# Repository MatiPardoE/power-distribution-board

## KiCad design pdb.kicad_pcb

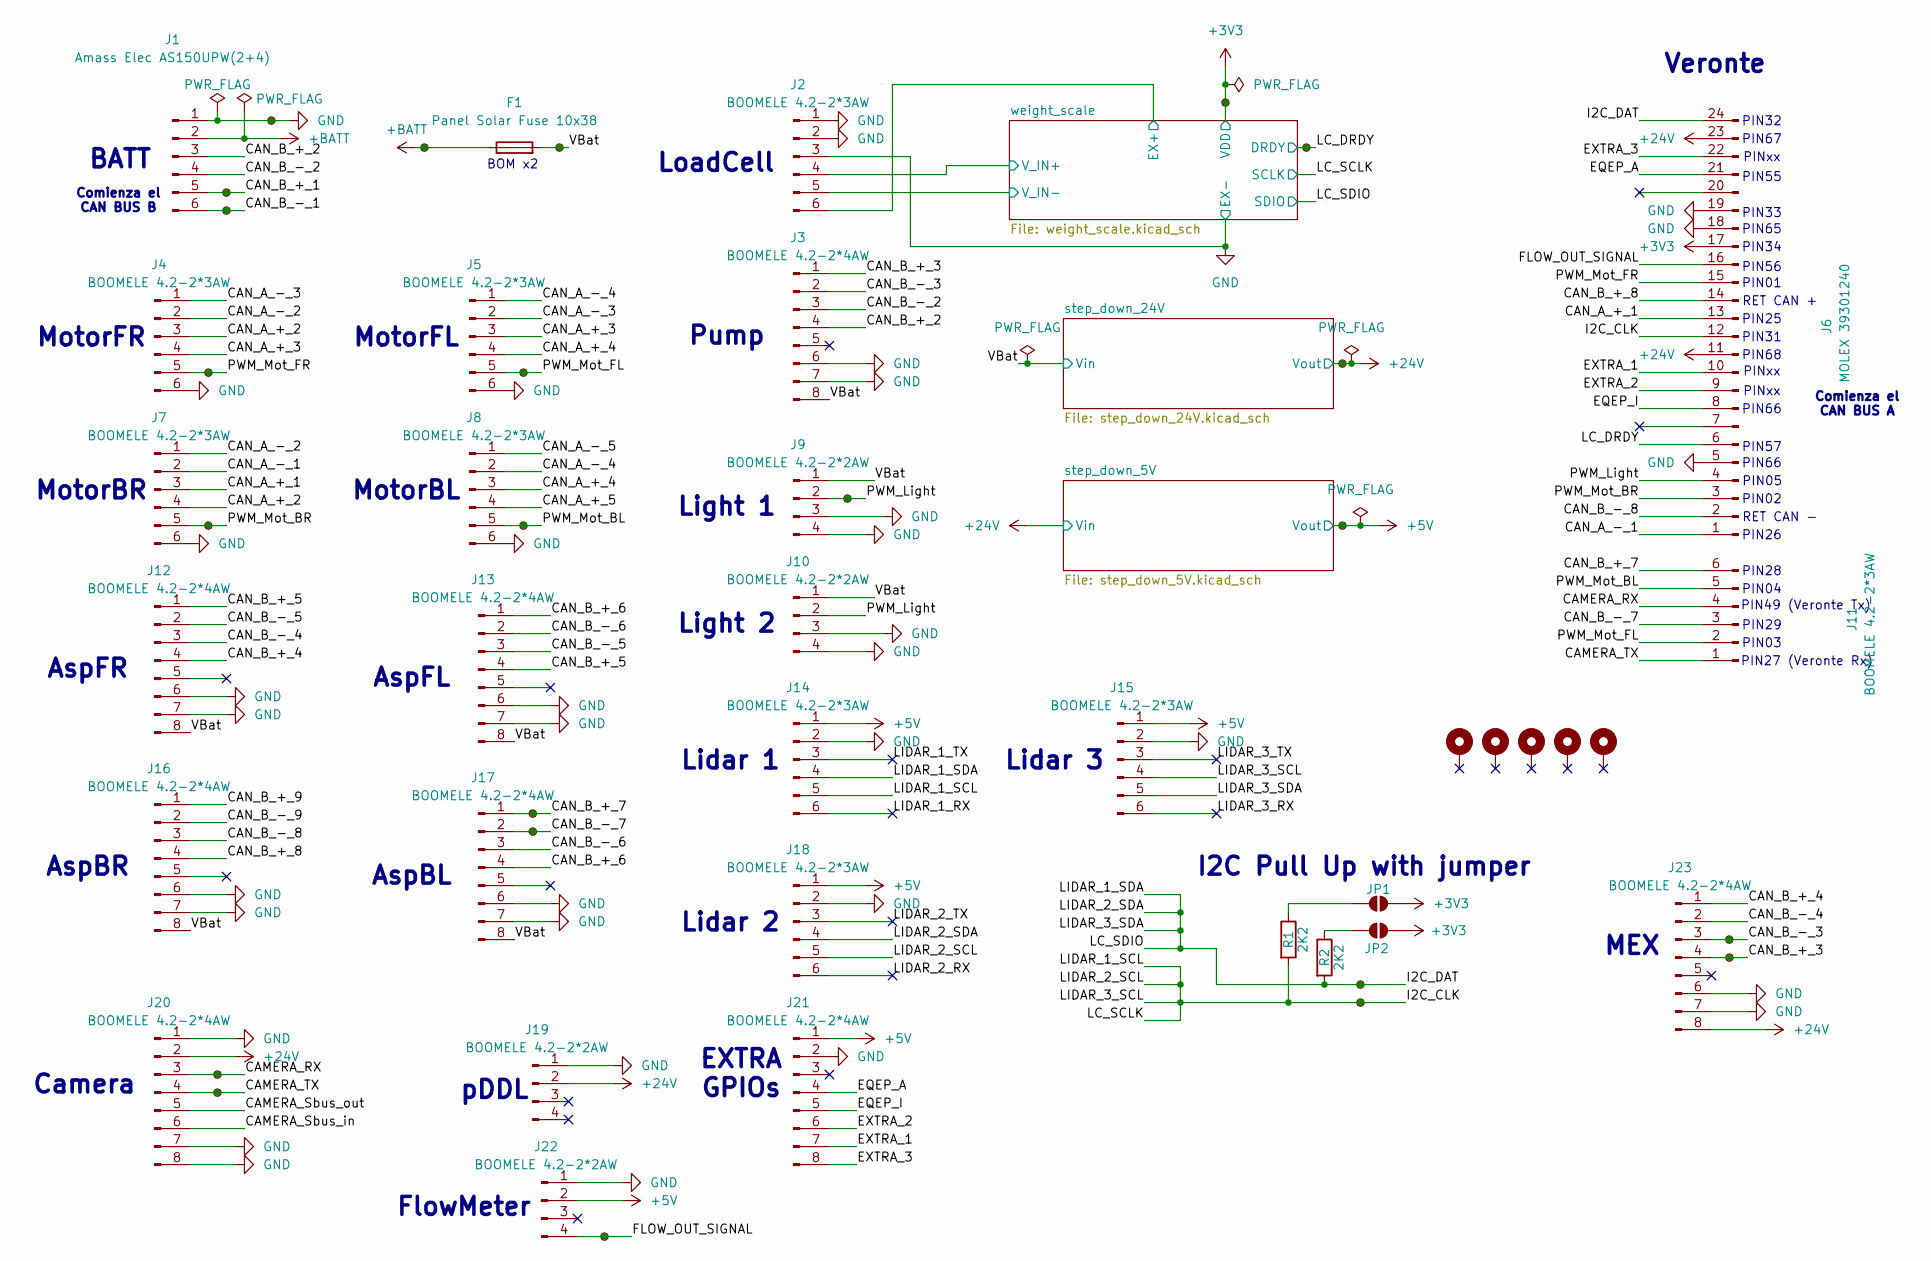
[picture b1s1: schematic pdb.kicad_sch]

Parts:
F1: Panel Solar Fuse 10x38; FUSE-HOLDER XFCN XF-008; LCSC Part # C717029
H1, H2, H3, H4, H5: MountingHole_Pad; MountingHole_3.2mm_M3_Pad_Via
J1: Amass Elec AS150UPW(2+4); CONN-TH_AS150UPW; LCSC Part # C19268054
J2, J4, J5, J7, J8, J11, J14, J15, J18: BOOMELE 4.2-2*3AW; Molex_Mini-Fit_Jr_5569-06A2_2x03_P4.20mm_Horizontal; LCSC Part # C54904
J3, J12, J13, J16, J17, J20, J21, J23: BOOMELE 4.2-2*4AW; Molex_Mini-Fit_Jr_5569-08A2_2x04_P4.20mm_Horizontal; LCSC Part # C44253
J6: MOLEX 39301240; Molex_Mini-Fit_Jr_5569-24A2_2x12_P4.20mm_Horizontal; LCSC Part # C492347
J9, J10, J19, J22: BOOMELE 4.2-2*2AW; Molex_Mini-Fit_Jr_5569-04A2_2x02_P4.20mm_Horizontal; LCSC Part # C54909
JP1, JP2: SolderJumper_2_Open; SolderJumper-2_P1.3mm_Open_TrianglePad1.0x1.5mm
R1, R2: 2K2; R_1206_3216Metric; LCSC Part # C2907443
TP1: +BATT; TestPoint_Pad_D2.0mm_silk_value
TP2: VBat; TestPoint_Pad_D2.0mm_silk_value
TP3: GND; TestPoint_Pad_D2.0mm_silk_value
TP4: CAN_B_+_1; TestPoint_Pad_D2.0mm_silk_value
TP5: CAN_B_-_1; TestPoint_Pad_D2.0mm_silk_value
TP8: CAN_B_+_7; TestPoint_Pad_D2.0mm_silk_value
TP9: CAN_B_-_7; TestPoint_Pad_D2.0mm_silk_value
TP12: CAM_RX; TestPoint_Pad_D2.0mm_silk_value
TP13: CAM_TX; TestPoint_Pad_D2.0mm_silk_value
TP14: PWM_MOT_FR; TestPoint_Pad_D2.0mm_silk_value
TP15: PWM_MOT_BR; TestPoint_Pad_D2.0mm_silk_value
TP16: PWM_MOT_BL; TestPoint_Pad_D2.0mm_silk_value
TP17: PWM_MOT_FL; TestPoint_Pad_D2.0mm_silk_value
TP18: FLOW_S; TestPoint_Pad_D2.0mm_silk_value
TP19: PWM_LIGHT; TestPoint_Pad_D2.0mm_silk_value
TP20: +24V; TestPoint_Pad_D2.0mm_silk_value
TP21: +5V; TestPoint_Pad_D2.0mm_silk_value
TP22: +3V3; TestPoint_Pad_D2.0mm_silk_value
TP23: I2C_DAT; TestPoint_Pad_D2.0mm_silk_value
TP24: I2C_CLK; TestPoint_Pad_D2.0mm_silk_value
TP27: LC_DRDY; TestPoint_Pad_D2.0mm_silk_value
TP28: CAN_B_-_3; TestPoint_Pad_D2.0mm_silk_value
TP29: CAN_B_+_3; TestPoint_Pad_D2.0mm_silk_value

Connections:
+3V3: J6.17, JP1.2 (B), JP2.2 (B), TP22.1; also elsewhere on the board
+5V: J14.1, J15.1, J18.1, J21.1, J22.2, TP21.1; also elsewhere on the board
+24V: J6.11, J6.23, J19.2, J20.2, J23.8, TP20.1; also elsewhere on the board
+BATT: F1.1, J1.2, TP1.1
/CAMERA_RX: J11.4, J20.3, TP12.1
/CAMERA_Sbus_in: J20.6
/CAMERA_Sbus_out: J20.5
/CAMERA_TX: J11.1, J20.4, TP13.1
/CAN_A_+_1: J6.13, J7.3
/CAN_A_+_2: J4.3, J7.4
/CAN_A_+_3: J4.4, J5.3
/CAN_A_+_4: J5.4, J8.3
/CAN_A_+_5: J8.4
/CAN_A_-_1: J6.1, J7.2
/CAN_A_-_2: J4.2, J7.1
/CAN_A_-_3: J4.1, J5.2
/CAN_A_-_4: J5.1, J8.2
/CAN_A_-_5: J8.1
/CAN_B_+_1: J1.5, TP4.1
/CAN_B_+_2: J1.3, J3.4
/CAN_B_+_3: J3.1, J23.4, TP29.1
/CAN_B_+_4: J12.4, J23.1
/CAN_B_+_5: J12.1, J13.4
/CAN_B_+_6: J13.1, J17.4
/CAN_B_+_7: J11.6, J17.1, TP8.1
/CAN_B_+_8: J6.14, J16.4
/CAN_B_+_9: J16.1
/CAN_B_-_1: J1.6, TP5.1
/CAN_B_-_2: J1.4, J3.3
/CAN_B_-_3: J3.2, J23.3, TP28.1
/CAN_B_-_4: J12.3, J23.2
/CAN_B_-_5: J12.2, J13.3
/CAN_B_-_6: J13.2, J17.3
/CAN_B_-_7: J11.3, J17.2, TP9.1
/CAN_B_-_8: J6.2, J16.3
/CAN_B_-_9: J16.2
/EQEP_A: J6.21, J21.4
/EQEP_I: J6.8, J21.5
/EXTRA_1: J6.10, J21.7
/EXTRA_2: J6.9, J21.6
/EXTRA_3: J6.22, J21.8
/FLOW_OUT_SIGNAL: J6.16, J22.4, TP18.1
/I2C_CLK: J6.12, J14.5, J15.4, J18.5, R1.2, TP24.1; also elsewhere on the board
/I2C_DAT: J6.24, J14.4, J15.5, J18.4, R2.2, TP23.1; also elsewhere on the board
/LC_DRDY: J6.6, TP27.1; also elsewhere on the board
/LIDAR_1_RX: J14.6
/LIDAR_1_TX: J14.3
/LIDAR_2_RX: J18.6
/LIDAR_2_TX: J18.3
/LIDAR_3_RX: J15.6
/LIDAR_3_TX: J15.3
/PWM_Light: J6.4, J9.2, J10.2, TP19.1
/PWM_Mot_BL: J8.5, J11.5, TP16.1
/PWM_Mot_BR: J6.3, J7.5, TP15.1
/PWM_Mot_FL: J5.5, J11.2, TP17.1
/PWM_Mot_FR: J4.5, J6.15, TP14.1
/VBat: F1.2, J3.8, J9.1, J10.1, J12.8, J13.8, J16.8, J17.8, TP2.1; also elsewhere on the board
/weight_scale/EX+: J2.6; also elsewhere on the board
/weight_scale/V_IN+: J2.4; also elsewhere on the board
/weight_scale/V_IN-: J2.5; also elsewhere on the board
GND: J1.1, J2.1, J2.2, J2.3, J3.6, J3.7, J4.6, J5.6, J6.5, J6.18, J6.19, J7.6, J8.6, J9.3, J9.4, J10.3, J10.4, J12.6, J12.7, J13.6, J13.7, J14.2, J15.2, J16.6, J16.7, J17.6, J17.7, J18.2, J19.1, J20.1, J20.7, J20.8, J21.2, J22.1, J23.6, J23.7, TP3.1; also elsewhere on the board
unnamed: JP1.1 (A), R1.1
unnamed: JP2.1 (A), R2.1

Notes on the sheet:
AspBR
FlowMeter
PIN66
PIN49 (Veronte Tx)
AspFR
PIN02
AspFL
PIN33
PIN01
PIN67
PIN56
PIN68
PINxx
Lidar 3
Light 1
Comienza el CAN BUS A
LoadCell
Lidar 1
I2C Pull Up with jumper
pDDL
MotorBR
Lidar 2
EXTRA GPIOs
Comienza el CAN BUS B
MotorBL
PIN32
PIN04
PIN57
PIN29
PIN31
MotorFR
MEX
PIN26
PIN27 (Veronte Rx)
PIN05
PIN28
Pump
Veronte
PIN55
Camera

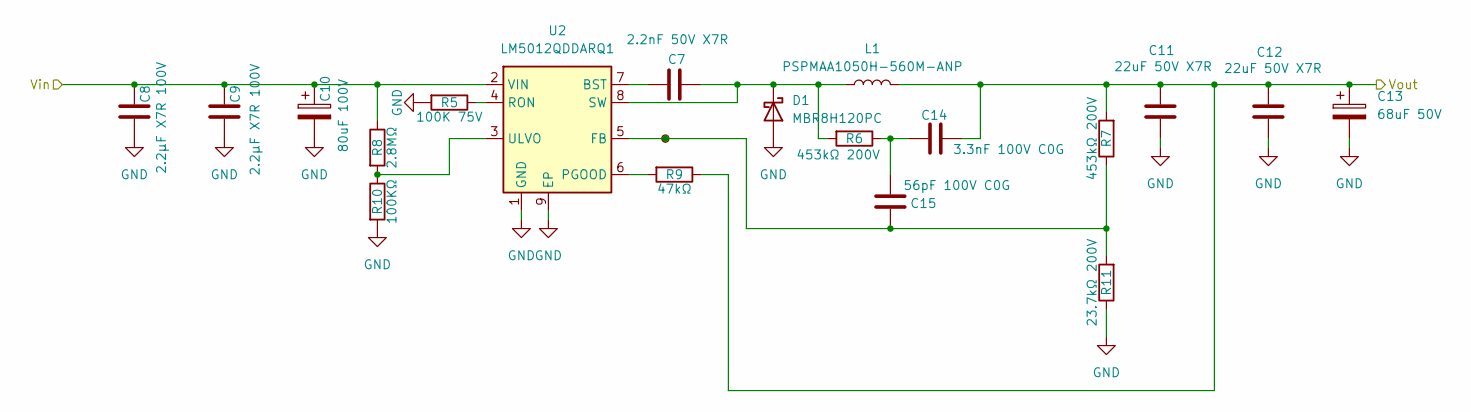
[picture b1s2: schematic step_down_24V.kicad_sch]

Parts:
C7: 2.2nF 50V X7R; C_0603_1608Metric; LCSC Part # C86023
C8, C9: 2.2µF X7R 100V; C_1206_3216Metric; LCSC Part # C577211
C10: 80uF 100V; CP_Elec_10x10.5; LCSC Part # C22387789
C11, C12: 22uF 50V X7R; C_1812_4532Metric; LCSC Part # C22388553
C13: 68uF 50V; CP_Elec_6.3x7.7; LCSC Part # C5221836
C14: 3.3nF 100V C0G; C_1206_3216Metric; LCSC Part # C2915710
C15: 56pF 100V C0G; C_0603_1608Metric; LCSC Part # C490535
D1: MBR8H120PC; TO-277C; LCSC Part # C19845038
L1: PSPMAA1050H-560M-ANP; L_Sunlord_MWSA1005S; LCSC Part # C5273831
R5: 100K 75V; R_0603_1608Metric; LCSC Part # C25803
R6, R7: 453kΩ 200V; R_1206_3216Metric; LCSC Part # C2085565
R8: 2.8MΩ; R_1206_3216Metric; LCSC Part # C488723
R9: 47kΩ; R_0805_2012Metric; LCSC Part # C17713
R10: 100KΩ; R_1206_3216Metric; LCSC Part # C17900
R11: 23.7kΩ 200V; R_1206_3216Metric; LCSC Part # C2085565
TP25: FB_24V; TestPoint_Pad_D2.0mm_silk_value
U2: LM5012QDDARQ1; SOIC-8-1EP_3.9x4.9mm_P1.27mm_EP2.95x4.9mm_Mask2.71x3.4mm_Th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; LCSC Part # C5451792

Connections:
+24V: C11.2, C12.2, C13.1, C14.1, L1.2, R7.2, R9.1; also elsewhere on the board
/VBat: C8.1, C9.1, C10.1, R8.1, U2.2 (VIN); also elsewhere on the board
GND: C8.2, C9.2, C10.2, C11.1, C12.1, C13.2, D1.2 (A), R5.2, R10.2, R11.1, U2.1 (GND), U2.9 (EP); also elsewhere on the board
unnamed: C14.2, C15.1, R6.1
unnamed: C7.2, D1.1 (K), L1.1, R6.2, U2.8 (SW)
unnamed: C7.1, U2.7 (BST)
unnamed: C15.2, R7.1, R11.2, TP25.1, U2.5 (FB)
unnamed: R9.2, U2.6 (PGOOD)
unnamed: R5.1, U2.4 (RON)
unnamed: R8.2, R10.1, U2.3 (ULVO)

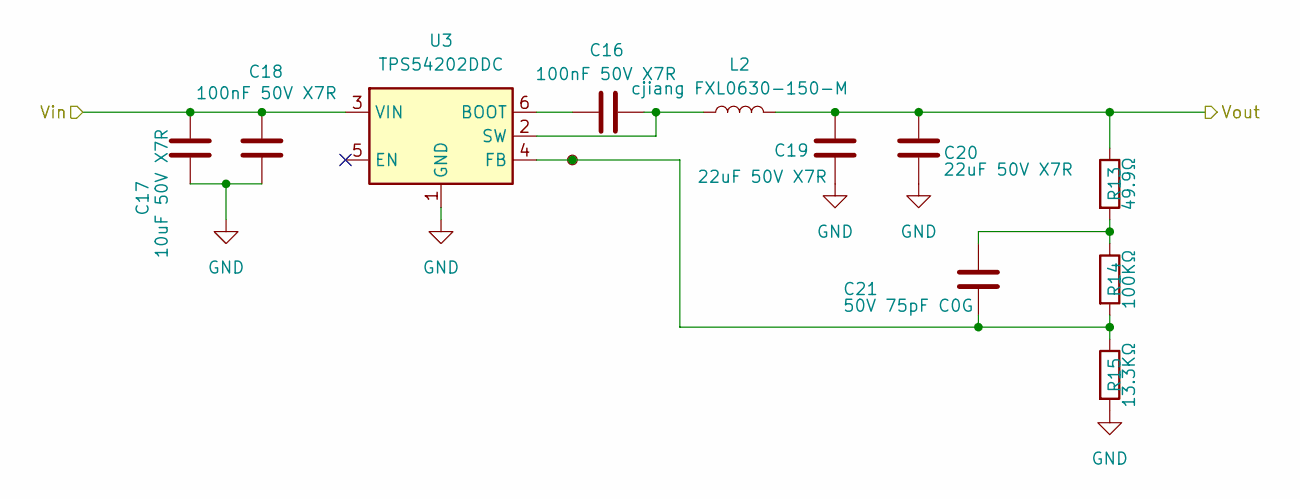
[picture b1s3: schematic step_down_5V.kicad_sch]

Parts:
C16, C18: 100nF 50V X7R; C_0603_1608Metric; LCSC Part # C14663
C17: 10uF 50V X7R; C_1206_3216Metric; LCSC Part # C89632
C19, C20: 22uF 50V X7R; C_1812_4532Metric; LCSC Part # C22388553
C21: 50V 75pF C0G; C_0603_1608Metric; LCSC Part # C1681
L2: cjiang FXL0630-150-M; L_Sunlord_MWSA0624S; LCSC Part # C177243
R13: 49.9Ω; R_1206_3216Metric; LCSC Part # C18018
R14: 100KΩ; R_1206_3216Metric; LCSC Part # C728669
R15: 13.3KΩ; R_1206_3216Metric; LCSC Part # C870412
TP26: FB_5V; TestPoint_Pad_D2.0mm_silk_value
U3: TPS54202DDC; SOT-23-6

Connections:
+5V: C19.2, C20.2, L2.2, R13.1; also elsewhere on the board
+24V: C17.2, C18.1, U3.3 (VIN); also elsewhere on the board
GND: C17.1, C18.2, C19.1, C20.1, R15.2, U3.1 (GND); also elsewhere on the board
unnamed: C21.2, R13.2, R14.1
unnamed: C16.1, U3.6 (BOOT)
unnamed: C21.1, R14.2, R15.1, TP26.1, U3.4 (FB)
unnamed: C16.2, L2.1, U3.2 (SW)

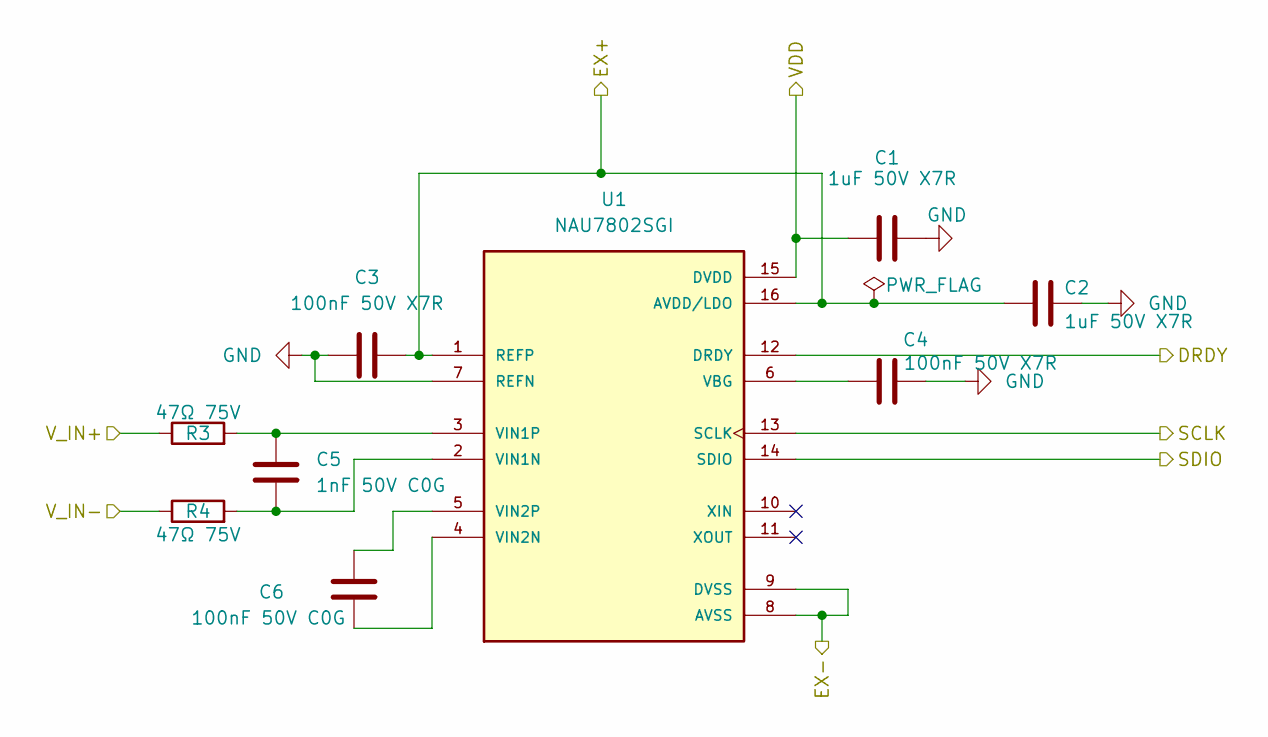
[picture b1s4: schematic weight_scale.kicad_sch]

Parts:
C1, C2: 1uF 50V X7R; C_0603_1608Metric; LCSC Part # C5199872
C3, C4: 100nF 50V X7R; C_0603_1608Metric; LCSC Part # C14663
C5: 1nF 50V C0G; C_0603_1608Metric; LCSC Part # C163508
C6: 100nF 50V C0G; C_1206_3216Metric; LCSC Part # C97946
R3, R4: 47Ω 75V; R_0603_1608Metric; LCSC Part # C1211
U1: NAU7802SGI; SOIC-16_3.9x9.9mm_P1.27mm; PARTREV 2.6; LCSC Part # C2614351

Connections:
+3V3: C1.1, U1.15 (DVDD); also elsewhere on the board
/I2C_CLK: U1.13 (SCLK); also elsewhere on the board
/I2C_DAT: U1.14 (SDIO); also elsewhere on the board
/LC_DRDY: U1.12 (DRDY); also elsewhere on the board
/weight_scale/EX+: C2.2, C3.1, U1.1 (REFP), U1.16 (AVDD/LDO); also elsewhere on the board
/weight_scale/V_IN+: R3.1; also elsewhere on the board
/weight_scale/V_IN-: R4.1; also elsewhere on the board
GND: C1.2, C2.1, C3.2, C4.2, U1.7 (REFN), U1.8 (AVSS), U1.9 (DVSS); also elsewhere on the board
unnamed: C4.1, U1.6 (VBG)
unnamed: C5.2, R4.2, U1.2 (VIN1N)
unnamed: C5.1, R3.2, U1.3 (VIN1P)
unnamed: C6.1, U1.4 (VIN2N)
unnamed: C6.2, U1.5 (VIN2P)

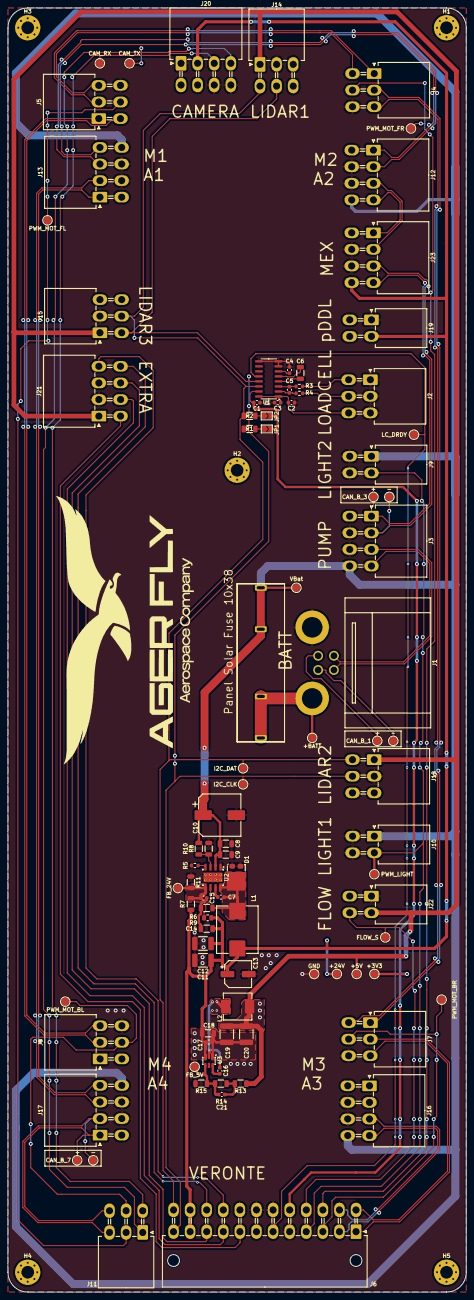
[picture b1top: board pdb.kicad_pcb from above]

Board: 2 copper layers, 116.0 x 325.0 mm, 97 parts (0 on the bottom side), 67 nets.

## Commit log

2026-01-07 Normalize line ending
2026-01-25 first commit branch
2026-01-26 ADD: Mas conectores al esquematico y fuse holder para 10x38
2026-01-29 Esquematico casi terminado falta agregar el veronte
2026-01-30 ADD: Fuente de 24V a 5V para los Lidar
2026-02-05 ADD: Terminado la fuente de 24V a 5V, terminado los pines del veronte y tambien el circuito de I2C
2026-02-05 FIX: Sensor de flujo en EQ
2026-02-15 Primer sesion de ruteo
2026-02-18 Agregado los testpoint, falta leds indicadores y serigrafia y cerramos
